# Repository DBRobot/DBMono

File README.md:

# DBMono

## Setup

After cloning, run the setup script from the repo root:

```bash
cd DBMono
./setup.sh
```

This will:
- Link KiCad templates to your local KiCad installation
- Set the `DBMONO_LIBS` environment variable in every installed KiCad version's
  config so that project library tables and 3D model paths using `${DBMONO_LIBS}`
  resolve to `<repo>/PCB_Hardware/libs`
- Link the VS Code C block-comment extension

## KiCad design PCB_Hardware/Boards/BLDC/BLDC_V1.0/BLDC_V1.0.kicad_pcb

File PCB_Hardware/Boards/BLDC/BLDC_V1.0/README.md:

# DBMono BLDC V1.0

This BLDC driver is designed as a general purpose brushless motor controller for robotics. Its focus is industrial grade performance at as low a cost as possible. Design requirements for this controller:
### Power
- Working voltage from 12-72V main input with daisy-chainable connectors
- Min 12A continuous current without cooling @60C
- 100A peak phase current
- Able to safely send regen current back to the bus or to a brake resistor
- Hot swap controller for safe hot plug and inrush control
- 5V logic input
- USBC logic input power delivery
- Short circuit protection
- Bidirectional reverse polarity protection
- Can survive +/- 100V transients

### Communication
- Daisy chain CANFD as the main communication interface
- USBC for configuration and live monitoring
- Dual SPI for up to 2 external encoders
- IO to support I2C, UART, ADC, TIM, and GPIO peripherals

### Sensing
- Onboard 21bit absolute magnetic encoder
- Onboard temperature sensor
- Optional off-board temperature sensor
- 4 Pin fan connector for PWM control and tachometer feedback

### Control Modes
- Sensorless FOC
- Position, velocity, and torque control
- Trajectory control
- Impedance control
- Anti-cogging compensation 
- Friction compensation
- Time synchronized commands
- Auto-tune

### Driver Parameters
- Switching  frequency of 45kHz

### Other
- ORing inputs for safe handling of multiple inputs
- EEPROM for configuration settings

## Gate Driver Design
The TI DRV8353SRTAR was selected for its low cost to performance and flexibility, as well as the high operating voltage. 
### FET Selection

#### Calculating Max $Q_g$ 
From 9.2.1.2.1 of the datasheet, the driver only supports fets that fall into the range given by the following equations:

![[Pasted image 20260510133448.png]] 

The design spec is up to 45kHz switching speed, and $I_{\text{VCP/VGLS}}$ is 25mA for all VM > 15V. While this design is technically specked to operate down to 12V, the target for performance is 24 and 48V motors. VM is fed by the input, so for the sake of this calculation the <15V scenario is ignored. 

**Trapezoidal Commutation**
$$
\begin{align}
&Q_g < \frac{I_{\text{VCP/VGLS}}}{f_{\text{PWM}}} \\
\\
&I_{\text{VCP/VGLS}} = 25mA \\
&f_{\text{PWM}} = 45kHz \\
\\
&Q_g < \frac{25 \times 10^{-3}\;A}{45 \times 10^3\;Hz}\\
&Q_g < 555\;nC
\end{align}
$$
**Sinusoidal Commutation**

$$
\begin{align}
&Q_g < \frac{I_{\text{VCP/VGLS}}}{3 \times f_{\text{PWM}}} \\
\\
&I_{\text{VCP/VGLS}} = 25mA \\
&f_{\text{PWM}} = 45kHz \\
\\
&Q_g < \frac{25 \times 10^{-3}\;A}{3 \times 45 \times 10^3\;Hz}\\
&Q_g < 185\;nC
\end{align}
$$

#### Calculating Max $R_{DS(ON)}$ 
From 9.2.1.2.3 in the datasheet, the overcurrent configuration is set via the equation bellow:

$$V_{DS\_OCP} > I_{max} \times R_{DS(ON)max}$$
As shown on the table in page 16 of the datasheet, the max setting for $V_{DS\_OCP}$ = 2V. Therefor:

$$
\begin{gathered}
R_{DS(ON)max} < \frac{V_{DS\_OCP}}{I_{max}} \\
\\
R_{DS(ON)max} < \frac{2V}{100A} \\
\\
R_{DS(ON)max} < 20m \Omega
\end{gathered}
$$

#### Selected FET - TPH3R70APL
This part was selected primarily for its thermal performance. In order to survive with 12A continuous current without a heat sink or other cooling solution, thermal performance is the most important aspect of fet selection. 

##### Min Rise Time
From the datasheet of the fet:

$$
Q_{gd}=14nC
$$

Then from the datasheet of the  DRV8353:
$$
\begin{array}{c c}
I_{DRIVEP} = \frac{Q_{gd}}{t_r} && I_{DRIVEN} = \frac{Q_{gd}}{t_f} \\
t_r > \frac{Q_{gd}}{I_{DRIVEP}} && t_f > \frac{Q_{gd}}{I_{DRIVEN}} \\
t_r > \frac{14nC}{1A} && t_f > \frac{14nC}{2A}\\
t_r > 14ns && t_f > 7ns
\end{array}
$$
##### Thermal Performance 
These calculations are done with no consideration for fans or other thermal management. This is done to establish the 12A no cooling baseline.

**Relevant Specs:**
$Q_g = 67nC < 185nC$
$T_{j\_max} = 175\degree C$ 
$R_{DS(ON)} \; @ \; T_{j\_max}= 9.25m\Omega$ 
$I_{peak} = I_D= 12 \times \sqrt 2 = 16.97A$
$t_r = 14ns$
$t_f = 19ns$

**Conduction Loss**
$$
\begin{gathered}
P_{cond} = I_{RMS}^2 \times R_{DS(ON)} \\
P_{cond} = (12A)^2 \times 0.00925 \Omega \\
P_{cond} = 1.33W
\end{gathered}
$$
**Switching Loss**
$$
\begin{gathered}
P_{sw} = \frac{1}{2} \times V_{BUS} \times I_D \times (t_r + t_f) \times f_{PWM} \\
P_{sw} = \frac{1}{2} \times 48V \times 16.97A \times  (14 \times 10^{-9} + 19 \times 10^{-9})s \times (45 \times 10^3) Hz \\
P_{sw} = 0.60W
\end{gathered}
$$

**Gate Charge Loss**
$$
\begin{gathered}
P_{gate} = Q_g \times V_{GS} \times f_{PWM} \\
P_{gate} = (67 \times 10^{-9})C \times 10V \times (45 \times 10^3)Hz \\
P_{gate} = 0.03W
\end{gathered}
$$

**Reverse Recovery Loss**

$$
\begin{gathered}
P_{rr} = Q_{rr} \times V_{BUS} \times f_{PWM} \\
P_{rr} = (74 \times 10^{-9})C \times 48V \times (45 \times 10^3)Hz \\
P_{rr} = 0.16W
\end{gathered}
$$
**Total Losses**
$$

P_{total} = 1.33 + 0.60 + 0.03 + 0.16 = 2.12W \\
$$
##### Copper Area Check
Using the total power loss of the FET, we can approximate the copper area needed to prevent the FET from failing. 

$$
\begin{gathered}
R_{\theta JA} < \frac{T_J - T_{ambient}}{P_{total}} \\
R_{\theta JA} < \frac{(175 - 60) \degree C}{2.12W} \\
R_{\theta JA} < 54.2 \degree C/W
\end{gathered}
$$

Application note Z8F80193346 from Infineon is used, as it is on a similar package, to sanity check the thermal limits given that there will be relatively little copper under each fet:
![[Pasted image 20260510212608.png]]

![[Pasted image 20260510212842.png]]
This implies that the board will need 12 thermal vias under the pad of the fet, with copper pour on both the top and bottom of them board. Single sided copper pour would be ill advised, but 2 layers of copper pour on the outer side of the board should be enough to keep thermals in check.

### Sense Amplifier Configuration
The DRV8353 uses shunt resistors to measure the current of each phase. To determine the resistance and gain values to use, the centered usable output voltage swing that the MCU can measure. Because a STM32G4 is used, $V_{VREF}=3.3V$.
$$
\begin{gathered}
V_O = (V_{VREF} - 0.25V) -\frac{V_{VREF}}{2} \\ \\
V_O = (3.3V-0.25V) - \frac{3.3V}{2} \\
V_O = 1.4V
\end{gathered}
$$

After calculating $V_O$, the resistance value $R$ can be calculated, where $A_V$ is the amplifier gain:

$$
\begin{aligned}
R &= \frac{V_O}{A_V \times I} & P_{SENSE} &> I_{RMS}^2 \times R 
\end{aligned}
$$

| | $A_V=5$ | $A_V=10$ | $A_V=20$ | $A_V=40$ |
|---|---|---|---|---|
| $R$ | $2.8m\Omega$ | $1.4m\Omega$ | $0.7m\Omega$ | $0.35m\Omega$ |
| $P_{SENSE}$ | $0.40W$ | $0.20W$ | $0.10W$ | $0.05W$ |
| $V_{DIFF}$ | $0.28V$ | $0.14V$ | $0.07V$ | $0.04V$ |

**Selected:** $A_V = 10$ with $R = 1m\Omega$. At $I_{max} = 100A$, $V_O = 1m\Omega \times 10 \times 100A = 1.0V$, keeping the amplifier output in the linear range with $0.4V$ of headroom in each direction. $1m\Omega$ is a standard value and $P_{SENSE} = 0.14W$ is easily handled by a 2512 package.

### DRV8353 Power Dissipation
Equations 26 and 27 from page 70 of the datasheet can be used to ensure that the gate driver itself does not overheat:

$$
\begin{aligned}
P_{VCP} &= I_{VCP} \times (V_{VM}+V_{VDRAIN}) & P_{VGLS} &= I_{VGLS} \times V_{VM} & P_{VM} &= I_{VM} \times V_{VM} \\
P_{VCP} &= 9mA \times (72V + 72V) & P_{VGLS} &= 9mA \times 72V & P_{VM} &= 15mA \times 72V \\
P_{VCP} &= 1.3W & P_{VGLS} &= 0.65W & P_{VM} &= 1.08W 
\end{aligned}
$$
$$
\begin{gathered}
P_{TOTAL} = 1.3W + 0.65W + 1.08W = 3.03W \\ 
R_{\theta JA} = 26.1 \\ \\
T_J = T_A + R_{\theta JA} \times P_{TOTAL} \\
T_J = 60 \degree C + (26.1 \times 3.03W) \\
T_J = 139 \degree C <150 \degree C
\end{gathered}
$$
### Input Bulk Capacitor

The DC link capacitor has two distinct jobs:

1. **Switching frequency bypass** (45kHz) — low-ESR MLCCs handle this trivially. Each 1206 MLCC handles $\sim 2A_{RMS}$ ripple. Only 3-4 are needed.
2. **Low-frequency energy storage** ($2\times$ electrical frequency, $\sim 100-1000$ Hz) — this drives the total capacitance. For a 12A motor at low speed, the DC link ripple current at $2\times f_e$ can be $4-6A_{RMS}$.

The DC bus current at 12A RMS phase current:

$$
I_{BUS} \approx \frac{3 \times V_{PHASE} \times I_{PHASE} \times \cos\phi}{V_{BUS} \times \eta}
\approx \frac{3 \times 26V \times 12A \times 0.9}{48V \times 0.9} \approx 20A
$$

Worst case switching-frequency ripple at $D=0.5$:

$$
C = \frac{I_{BUS} \times 0.25}{f_{PWM} \times \Delta V}
$$

| Condition | $I_{BUS}$ | $\Delta V=0.5V$ | $\Delta V=1V$ | $\Delta V=2V$ |
|---|---|---|---|---|
| 48V, 12A cont | 20A | $222\mu F$ | $111\mu F$ | $56\mu F$ |
| 72V, 12A cont | 14A | $156\mu F$ | $78\mu F$ | $39\mu F$ |
| 48V, 100A peak | 90A | $1000\mu F$ | $500\mu F$ | $250\mu F$ |

**Selected:**

| Part | Count | Value | Package | Purpose |
|------|-------|-------|---------|---------|
| C23 | 1 | $330\mu F$, 100V | Radial through-hole ($10\times 20$mm) | Bulk, handles $2\times f_e$ ripple |
| C25–C28 | 4 | $2.2\mu F$, 100V X7S | 1206 | Switching frequency bypass |
| CVM1 | 1 | $0.1\mu F$, 100V X7R | 0805 | Datasheet requirement at VM pin |

At 48V/12A: $\Delta V \approx 0.14V$ switching ripple, $\sim 3V$ peak at $2\times$ electrical frequency — well within DRV8353 headroom. At 100A peak transient: $\Delta V \approx 0.7V$. A single radial electrolytic is smaller than two 100V SMD equivalents, simpler to route, and handles the ripple current adequately since the battery sinks most of the low-frequency content and the MLCCs handle the 45kHz content.

### Hot-Swap Precharge (LM5069MM-2)

The LM5069MM-2 (U5) controls inrush via Rsns (R6 = 0.5mΩ, 2512) and Ctimer (C11 = 33nF, 0402). The pass FET is Q2 = IPT015N10N5 (100V/300A).

**Current limit** (Datasheet §6.5, V_sns_th = 50mV typical):

$$
I_{LIM} = \frac{V_{SNS\_TH}}{R_{SNS}} = \frac{50\text{mV}}{0.5\text{m}\Omega} = 100\text{A}
$$

**Inrush charge time** with C_load ≈ 340µF:

$$
t_{CHARGE} = \frac{C_{LOAD} \times V_{IN}}{I_{LIM}}
$$

| $V_{IN}$ | $t_{CHARGE}$ |
|----------|-------------|
| 48V | $340\mu F \times 48V / 100A = 163\mu s$ |
| 72V | $340\mu F \times 72V / 100A = 245\mu s$ |

**Fault timer** (Datasheet §7.3.2, I_timer = 85µA typical, V_timer_th = 1.25V):

$$
t_{FAULT} = \frac{C_{TIMER} \times V_{TIMER\_TH}}{I_{TIMER}} = \frac{33\text{nF} \times 1.25\text{V}}{85\mu\text{A}} = 485\mu\text{s}
$$

**Margin check** — t_fault > t_charge with >2× margin across all conditions:

| Condition | t_charge | t_fault | Margin |
|-----------|----------|---------|--------|
| 48V | 163µs | 485µs | 3.0× |
| 72V | 245µs | 485µs | 2.0× |
| 72V, I_timer max (110µA) | 245µs | 375µs | 1.5× |

## Change Notes

 - C14/C24 - footprint size needs to get larger. 10uF caps dont exist in that size
 -

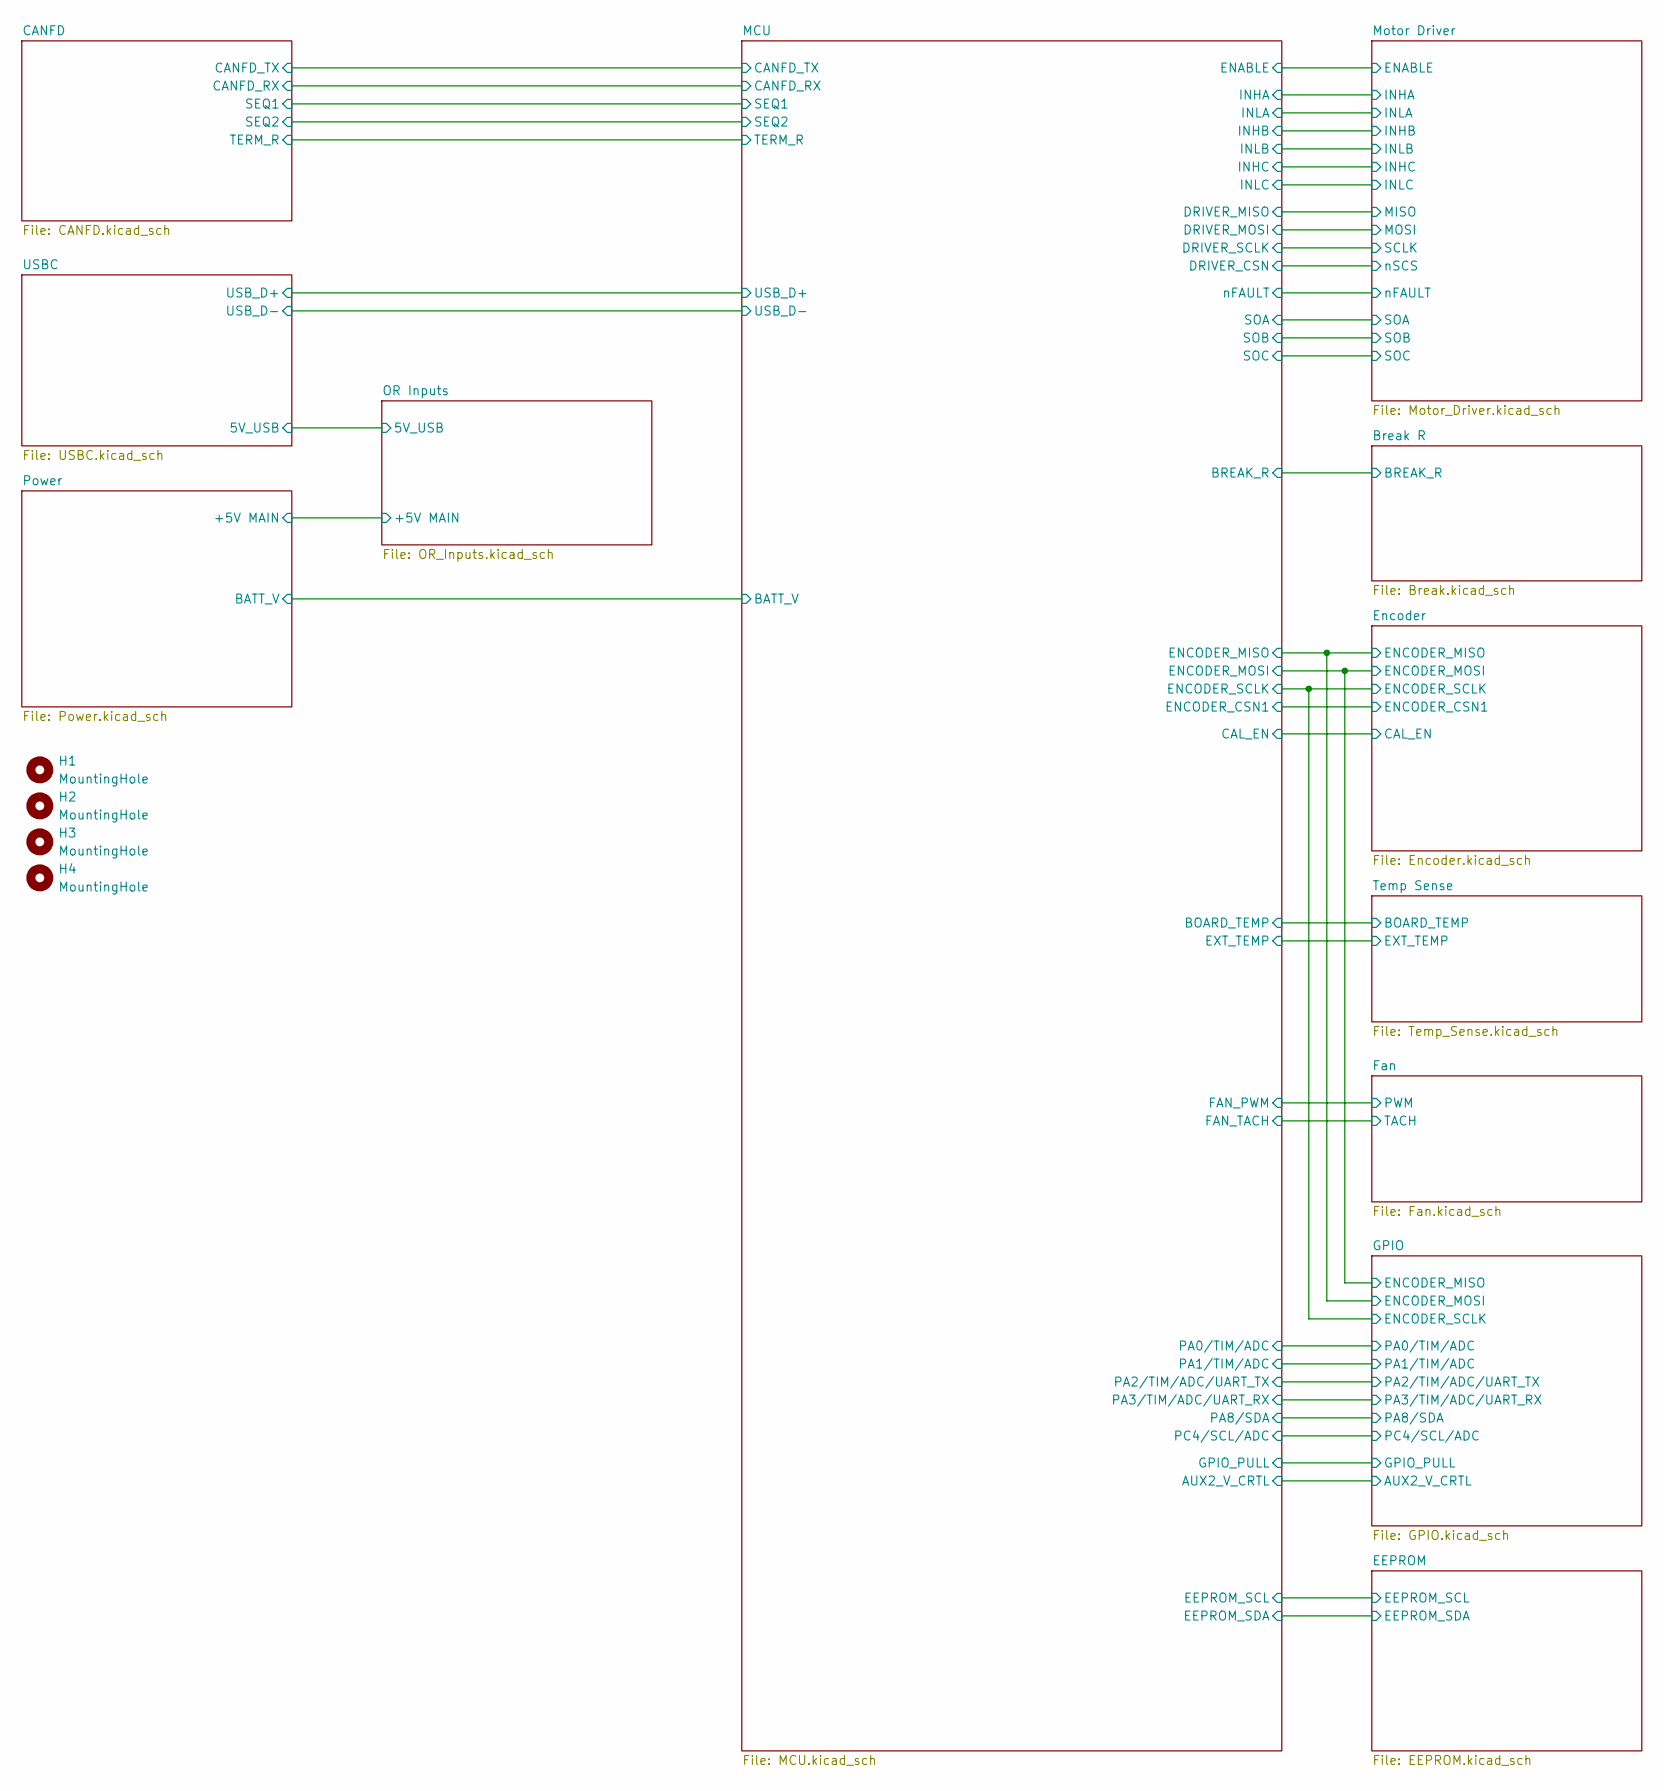
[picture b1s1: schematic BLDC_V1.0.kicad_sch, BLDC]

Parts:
H1, H2, H3, H4: MountingHole; MountingHole_3.2mm_M3

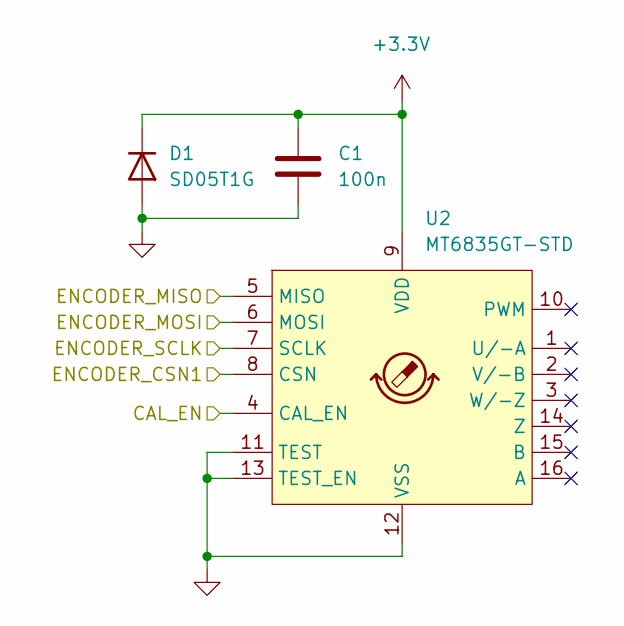
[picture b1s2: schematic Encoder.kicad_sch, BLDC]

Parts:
C1: 100n; C_0402_1005Metric; Manufacturer_Part_Number CC0402ZRY5V6BB104
D1: SD05T1G; D_SOD-323; Manufacturer_Part_Number SD05T1G
U2: MT6835GT-STD; TSSOP-16_4.4x5mm_P0.65mm; Manufacturer_Part_Number MT6835GT-STD

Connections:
+3.3V: C1.1, D1.1 (K), U2.9 (VDD); also elsewhere on the board
/Encoder/CAL_EN: U2.4 (CAL_EN); also elsewhere on the board
/Encoder/ENCODER_CSN1: U2.8 (CSN); also elsewhere on the board
/Encoder/ENCODER_MISO: U2.5 (MISO); also elsewhere on the board
/Encoder/ENCODER_MOSI: U2.6 (MOSI); also elsewhere on the board
/Encoder/ENCODER_SCLK: U2.7 (SCLK); also elsewhere on the board
GND: C1.2, D1.2 (A), U2.11 (TEST), U2.12 (VSS), U2.13 (TEST_EN); also elsewhere on the board

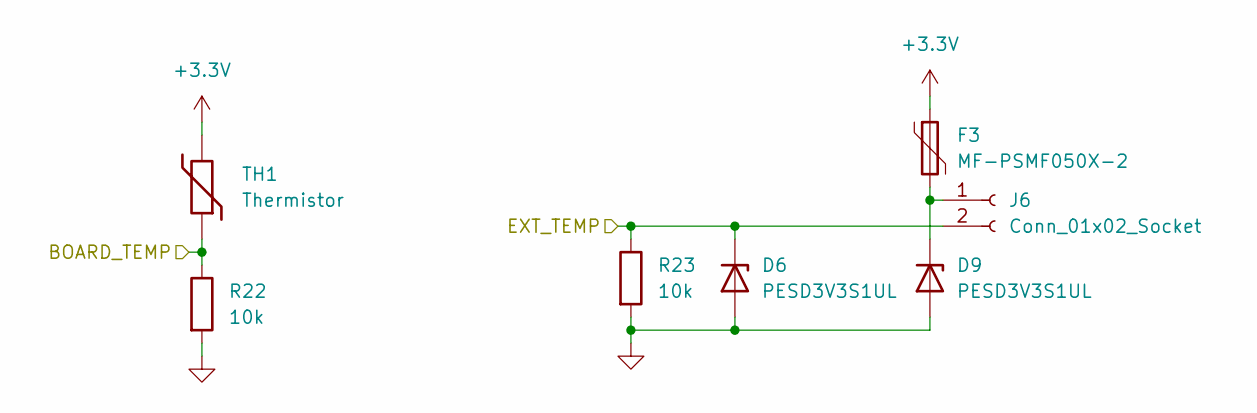
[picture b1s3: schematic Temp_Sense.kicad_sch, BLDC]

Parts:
D6, D9: PESD3V3S1UL; D_SOD-882
F3: MF-PSMF050X-2; Fuse_0805_2012Metric; Manufacturer_Part_Number MF-PSMF050X-2
J6: Conn_01x02_Socket; JST_GH_SM02B-GHS-TB_1x02-1MP_P1.25mm_Horizontal
R22, R23: 10k; R_0402_1005Metric; Manufacturer_Part_Number HP02WAJ0103TCE
TH1: Thermistor; R_0603_1608Metric

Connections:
+3.3V: F3.1, TH1.2; also elsewhere on the board
/MCU/BOARD_TEMP: R22.1, TH1.1; also elsewhere on the board
/MCU/EXT_TEMP: D6.1 (K), J6.2, R23.1; also elsewhere on the board
GND: D6.2 (A), D9.2 (A), R22.2, R23.2; also elsewhere on the board
unnamed: D9.1 (K), F3.2, J6.1

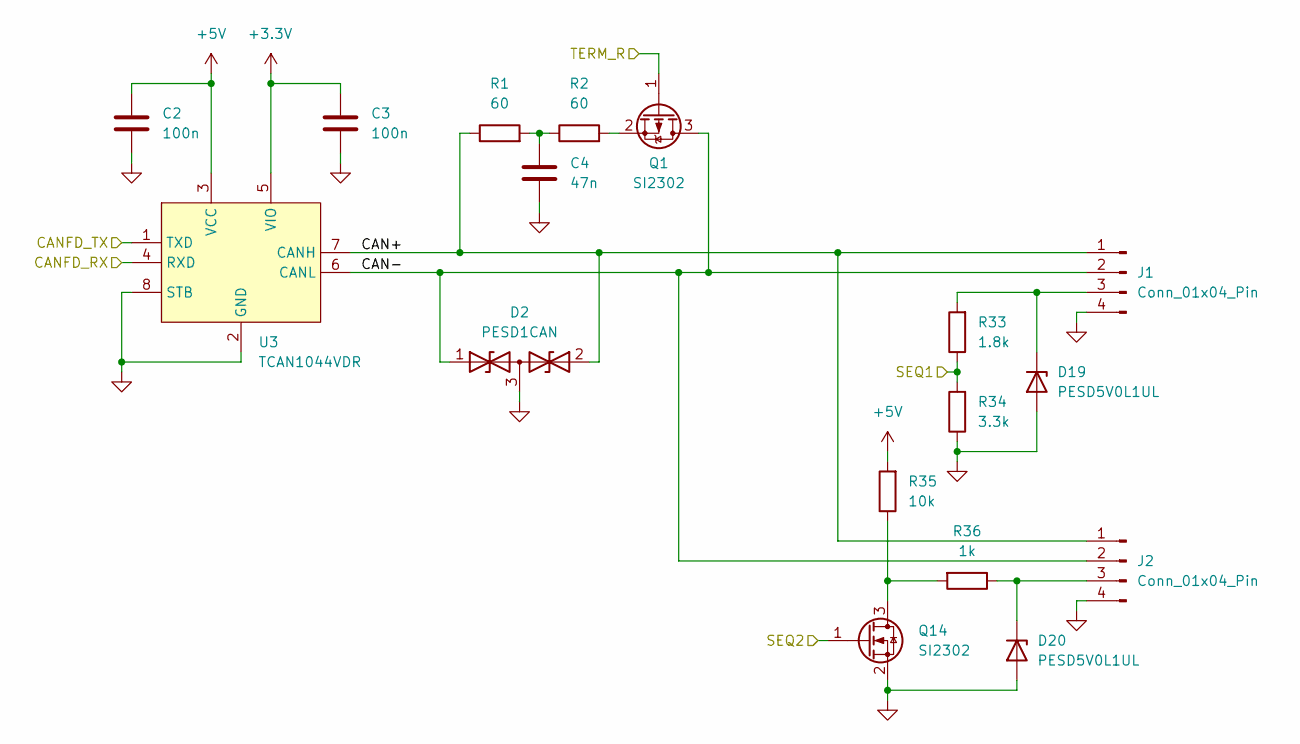
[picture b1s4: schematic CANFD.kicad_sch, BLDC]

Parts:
C2, C3: 100n; C_0402_1005Metric; Manufacturer_Part_Number CC0402ZRY5V6BB104
C4: 47n; C_0402_1005Metric; Manufacturer_Part_Number CC0402JRX7R6BB473
D2: PESD1CAN; SOT-23
D19, D20: PESD5V0L1UL; D_SOD-882
J1, J2: Conn_01x04_Pin; CONN_JST_SM04B-PASS; Manufacturer_Part_Number JST SM04B-PASS-TB(LF)(SN)
Q1, Q14: SI2302; SOT-23; Manufacturer_Part_Number Si2302CDS-T1-GE3
R1, R2: 60; R_0805_2012Metric; Manufacturer_Part_Number CQ05W8F604JT5E
R33: 1.8k; R_0402_1005Metric; Manufacturer_Part_Number 0402WGJ0182TCE
R34: 3.3k; R_0402_1005Metric; Manufacturer_Part_Number RC0402JR-073K3L
R35: 10k; R_0402_1005Metric; Manufacturer_Part_Number HP02WAJ0103TCE
R36: 1k; R_0402_1005Metric; Manufacturer_Part_Number CQ02WGJ0102TCE
U3: TCAN1044VDR; SOIC-8_3.9x4.9mm_P1.27mm; Manufacturer_Part_Number TCAN1044VDR

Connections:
+3.3V: C3.1, U3.5 (VIO); also elsewhere on the board
+5V: C2.1, R35.2, U3.3 (VCC); also elsewhere on the board
/CANFD/CAN+: D2.2 (A2), J1.1, J2.1, R1.1, U3.7 (CANH)
/CANFD/CAN-: D2.1 (A1), J1.2, J2.2, Q1.3 (D), U3.6 (CANL)
/CANFD/CANFD_RX: U3.4 (RXD); also elsewhere on the board
/CANFD/CANFD_TX: U3.1 (TXD); also elsewhere on the board
/CANFD/SEQ1: R33.1, R34.2; also elsewhere on the board
/CANFD/SEQ2: Q14.1 (G); also elsewhere on the board
/CANFD/TERM_R: Q1.1 (G); also elsewhere on the board
GND: C2.2, C3.2, C4.2, D2.3 (common), D19.2 (A), D20.2 (A), J1.4, J2.4, Q14.2 (S), R34.1, U3.2 (GND), U3.8 (STB); also elsewhere on the board
unnamed: C4.1, R1.2, R2.1
unnamed: D19.1 (K), J1.3, R33.2
unnamed: D20.1 (K), J2.3, R36.1
unnamed: Q1.2 (S), R2.2
unnamed: Q14.3 (D), R35.1, R36.2

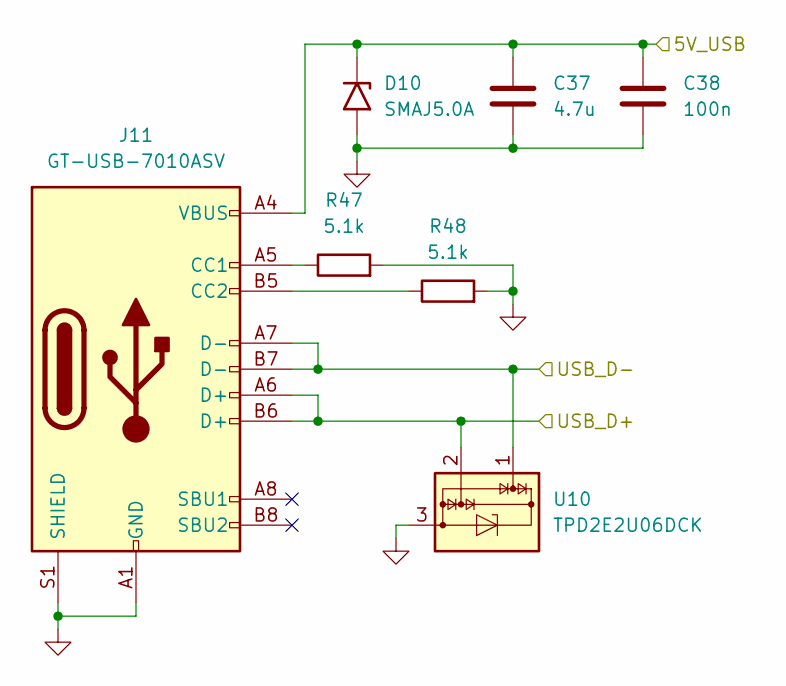
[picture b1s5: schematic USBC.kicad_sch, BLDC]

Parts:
C37: 4.7u; C_0603_1608Metric; Manufacturer_Part_Number CL10A475MQ8NNNC
C38: 100n; C_0402_1005Metric; Manufacturer_Part_Number CC0402ZRY5V6BB104
D10: SMAJ5.0A; D_SMA
J11: GT-USB-7010ASV; USB_C_Receptacle_G-Switch_GT-USB-7010ASV; Manufacturer_Part_Number GT-USB-7010ASV
R47, R48: 5.1k; R_0402_1005Metric; Manufacturer_Part_Number RC0402JR-075K1L
U10: TPD2E2U06DCK; SOT-323_SC-70; Manufacturer_Part_Number TPD2E2U06DCK

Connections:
/MCU/USB_D+: J11.A6 (D+), J11.B6 (D+), U10.2; also elsewhere on the board
/MCU/USB_D-: J11.A7 (D-), J11.B7 (D-), U10.1; also elsewhere on the board
/OR Inputs/5V_USB: C37.1, C38.1, D10.1 (A1), J11.A4 (VBUS), J11.A9 (VBUS), J11.B4 (VBUS), J11.B9 (VBUS); also elsewhere on the board
GND: C37.2, C38.2, D10.2 (A2), J11.A1 (GND), J11.A12 (GND), J11.B1 (GND), J11.B12 (GND), J11.S1 (SHIELD), R47.2, R48.2, U10.3; also elsewhere on the board
unnamed: J11.A5 (CC1), R47.1
unnamed: J11.B5 (CC2), R48.1

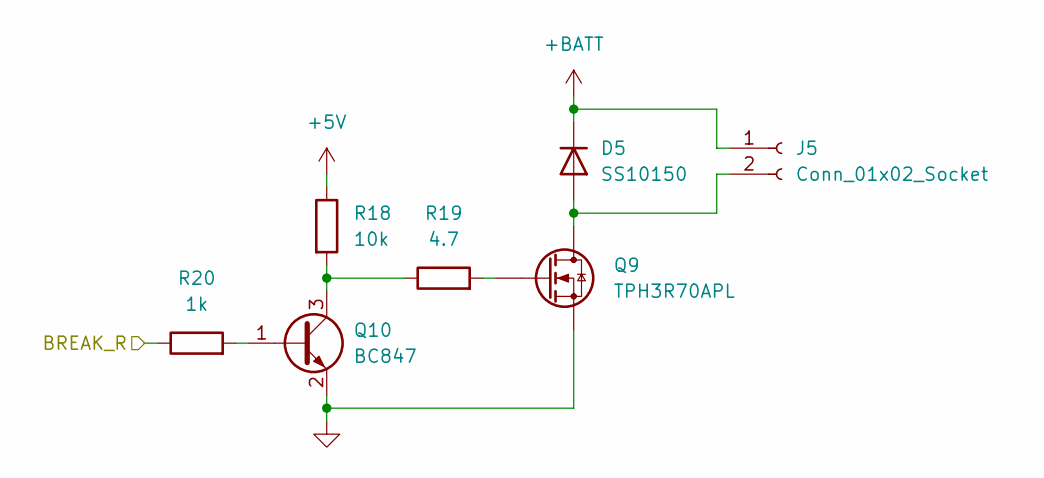
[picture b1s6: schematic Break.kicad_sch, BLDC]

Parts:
D5: SS10150; D_SOD-123F; Manufacturer_Part_Number SS10150
J5: Conn_01x02_Socket; JST_XH_S2B-XH-A-1_1x02_P2.50mm_Horizontal
Q9: TPH3R70APL; SOP AdvanceN_TOS; Manufacturer_Part_Number TPH3R70APL
Q10: BC847; SOT-23
R18: 10k; R_0402_1005Metric; Manufacturer_Part_Number HP02WAJ0103TCE
R19: 4.7; R_0402_1005Metric; Manufacturer_Part_Number 0402WGJ047JTCE
R20: 1k; R_0402_1005Metric; Manufacturer_Part_Number CQ02WGJ0102TCE

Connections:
+5V: R18.1; also elsewhere on the board
+BATT: D5.1 (K), J5.1; also elsewhere on the board
/Break R/BREAK_R: R20.1; also elsewhere on the board
GND: Q9.1 (S), Q9.2 (S), Q9.3 (S), Q10.2 (E); also elsewhere on the board
unnamed: D5.2 (A), J5.2, Q9.5 (D), Q9.6 (D), Q9.7 (D), Q9.8 (D)
unnamed: Q9.4 (G), R19.2
unnamed: Q10.1 (B), R20.2
unnamed: Q10.3 (C), R18.2, R19.1

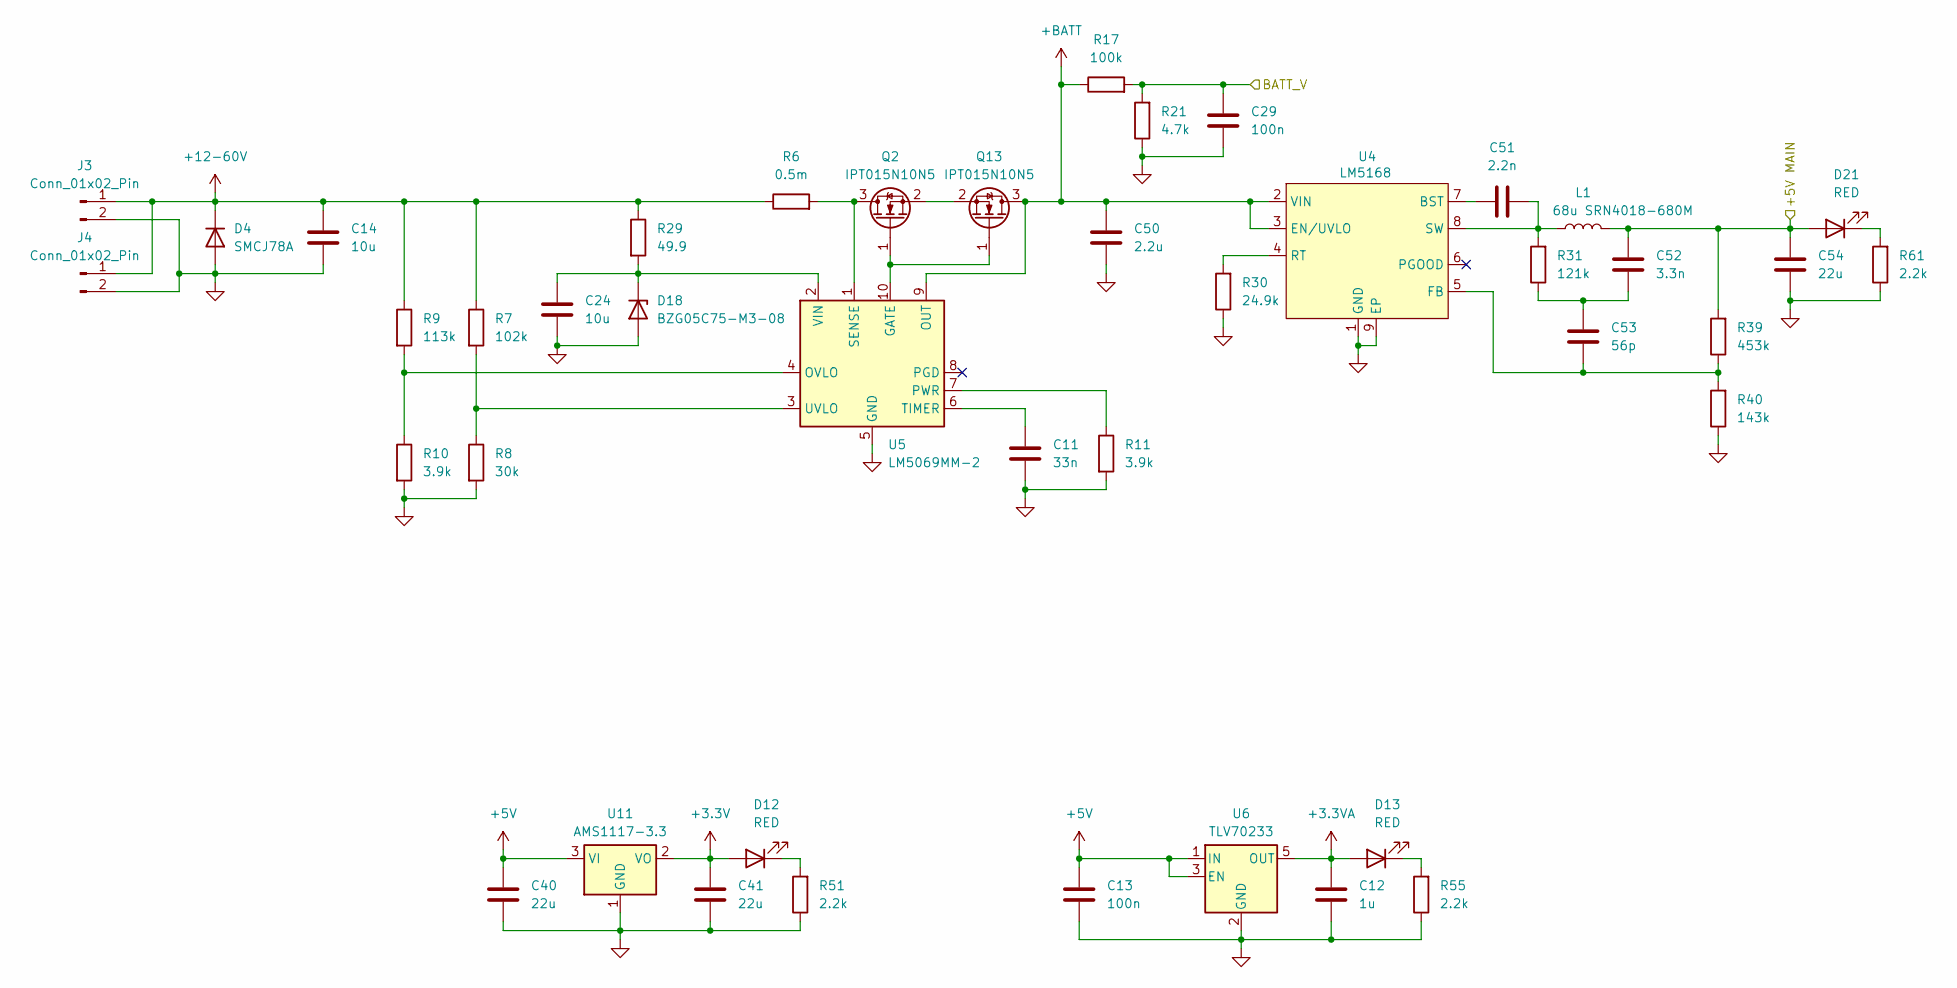
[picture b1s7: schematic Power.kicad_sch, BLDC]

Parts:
C11: 33n; C_0402_1005Metric; Manufacturer_Part_Number CC0402MRX7R7BB333
C12: 1u; C_0603_1608Metric; Manufacturer_Part_Number CC0603ZRY5V6BB105
C13: 100n; C_0402_1005Metric; Manufacturer_Part_Number CC0402ZRY5V6BB104
C14, C24: 10u; C_0603_1608Metric; Manufacturer_Part_Number JMK107BJ106KA-T
C29: 100n; C_0402_1005Metric; Manufacturer_Part_Number GRM155R62A104KE14D
C40, C41, C54: 22u; C_0805_2012Metric; Manufacturer_Part_Number CC0805KRX7R0BB681
C50: 2.2u; C_0805_2012Metric; Manufacturer_Part_Number GRM21BD72A225ME01L
C51: 2.2n; C_0402_1005Metric; Manufacturer_Part_Number CC0402MRX7R6BB222
C52: 3.3n; C_0402_1005Metric; Manufacturer_Part_Number CC0402KRX7R7BB332
C53: 56p; C_0402_1005Metric; Manufacturer_Part_Number CC0402GRNPO9BN560
D4: SMCJ78A; D_SMC
D12, D13, D21: RED; LED_0603_1608Metric; Manufacturer_Part_Number XINGLIGHT XL-1608SURC-06
D18: BZG05C75-M3-08; D_SMA; Manufacturer_Part_Number BZG05C75-M3-08
J3, J4: Conn_01x02_Pin; AMASS_XT30PW-M_1x02_P2.50mm_Horizontal; Manufacturer_Part_Number XT30PW-M30.G.Y
L1: 68u SRN4018-680M; L_Bourns-SRN4018; Manufacturer_Part_Number SRN4018-680M
Q2, Q13: IPT015N10N5; Infineon_PG-HSOF-8-1; Manufacturer_Part_Number IPT015N10N5
R6: 0.5m; R_2512_6332Metric; Manufacturer_Part_Number WSL2512L5000FEA18
R7: 102k; R_0805_2012Metric; Manufacturer_Part_Number 0805W8F1023T5E
R8: 30k; R_0805_2012Metric; Manufacturer_Part_Number 0805W8J0303T5E
R9: 113k; R_0805_2012Metric; Manufacturer_Part_Number 0805W8F1133T5E
R10: 3.9k; R_0805_2012Metric; Manufacturer_Part_Number 0805W8J0392T5E
R11: 3.9k; R_0402_1005Metric; Manufacturer_Part_Number CQ02WGF3901TCE
R17: 100k; R_0603_1608Metric; Manufacturer_Part_Number CQ03WAJ0104T5E
R21: 4.7k; R_0603_1608Metric; Manufacturer_Part_Number 0603WAF3032T5S
R29: 49.9; R_0805_2012Metric; Manufacturer_Part_Number 0805W8F499JT5E
R30: 24.9k; R_0402_1005Metric; Manufacturer_Part_Number RC0402FR-0724K9L
R31: 121k; R_0402_1005Metric; Manufacturer_Part_Number 0402WGF1213TCE
R39: 453k; R_0402_1005Metric; Manufacturer_Part_Number CRCW0402453KFKED
R40: 143k; R_0402_1005Metric; Manufacturer_Part_Number 0402WGF1433TCE
R51, R55, R61: 2.2k; R_0402_1005Metric; Manufacturer_Part_Number 0402WGJ0222TCE
U4: LM5168; SOIC-8-1EP_3.9x4.9mm_P1.27mm_EP2.29x3mm; Manufacturer_Part_Number LM5168
U5: LM5069MM-2; MSOP-10_3x3mm_P0.5mm; Manufacturer_Part_Number LM5069MM-2
U6: TLV70233; SOT-23-5; Manufacturer_Part_Number TLV70233
U11: AMS1117-3.3; SOT-223-3_TabPin2; Manufacturer_Part_Number AMS1117-3.3

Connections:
+3.3V: C41.1, D12.2 (A), U11.2 (VO); also elsewhere on the board
+3.3VA: C12.1, D13.2 (A), U6.5 (OUT); also elsewhere on the board
+5V: C13.1, C40.1, U6.1 (IN), U6.3 (EN), U11.3 (VI); also elsewhere on the board
+12-60V: C14.1, D4.1 (K), J3.1, J4.1, R6.1, R7.1, R9.1, R29.1
+BATT: C50.1, Q13.3 (D), R17.1, U4.2 (VIN), U4.3 (EN/UVLO), U5.9 (OUT); also elsewhere on the board
/MCU/BATT_V: C29.1, R17.2, R21.2; also elsewhere on the board
/OR Inputs/+5V MAIN: C52.2, C54.1, D21.2 (A), L1.2, R39.2; also elsewhere on the board
GND: C11.2, C12.2, C13.2, C14.2, C24.2, C29.2, C40.2, C41.2, C50.2, C54.2, D4.2 (A), D18.2 (A), J3.2, J4.2, R8.2, R10.2, R11.2, R21.1, R30.1, R40.1, R51.1, R55.1, R61.1, U4.1 (GND), U4.9 (EP), U5.5 (GND), U6.2 (GND), U11.1 (GND); also elsewhere on the board
unnamed: C52.1, C53.2, R31.1
unnamed: D12.1 (K), R51.2
unnamed: D13.1 (K), R55.2
unnamed: C24.1, D18.1 (K), R29.2, U5.2 (VIN)
unnamed: D21.1 (K), R61.2
unnamed: Q2.3 (D), R6.2, U5.1 (SENSE)
unnamed: Q2.1 (G), Q13.1 (G), U5.10 (GATE)
unnamed: Q2.2 (S), Q13.2 (S)
unnamed: C51.1, U4.7 (BST)
unnamed: C53.1, R39.1, R40.2, U4.5 (FB)
unnamed: R30.2, U4.4 (RT)
unnamed: C51.2, L1.1, R31.2, U4.8 (SW)
unnamed: R9.2, R10.1, U5.4 (OVLO)
unnamed: R11.1, U5.7 (PWR)
unnamed: C11.1, U5.6 (TIMER)
unnamed: R7.2, R8.1, U5.3 (UVLO)

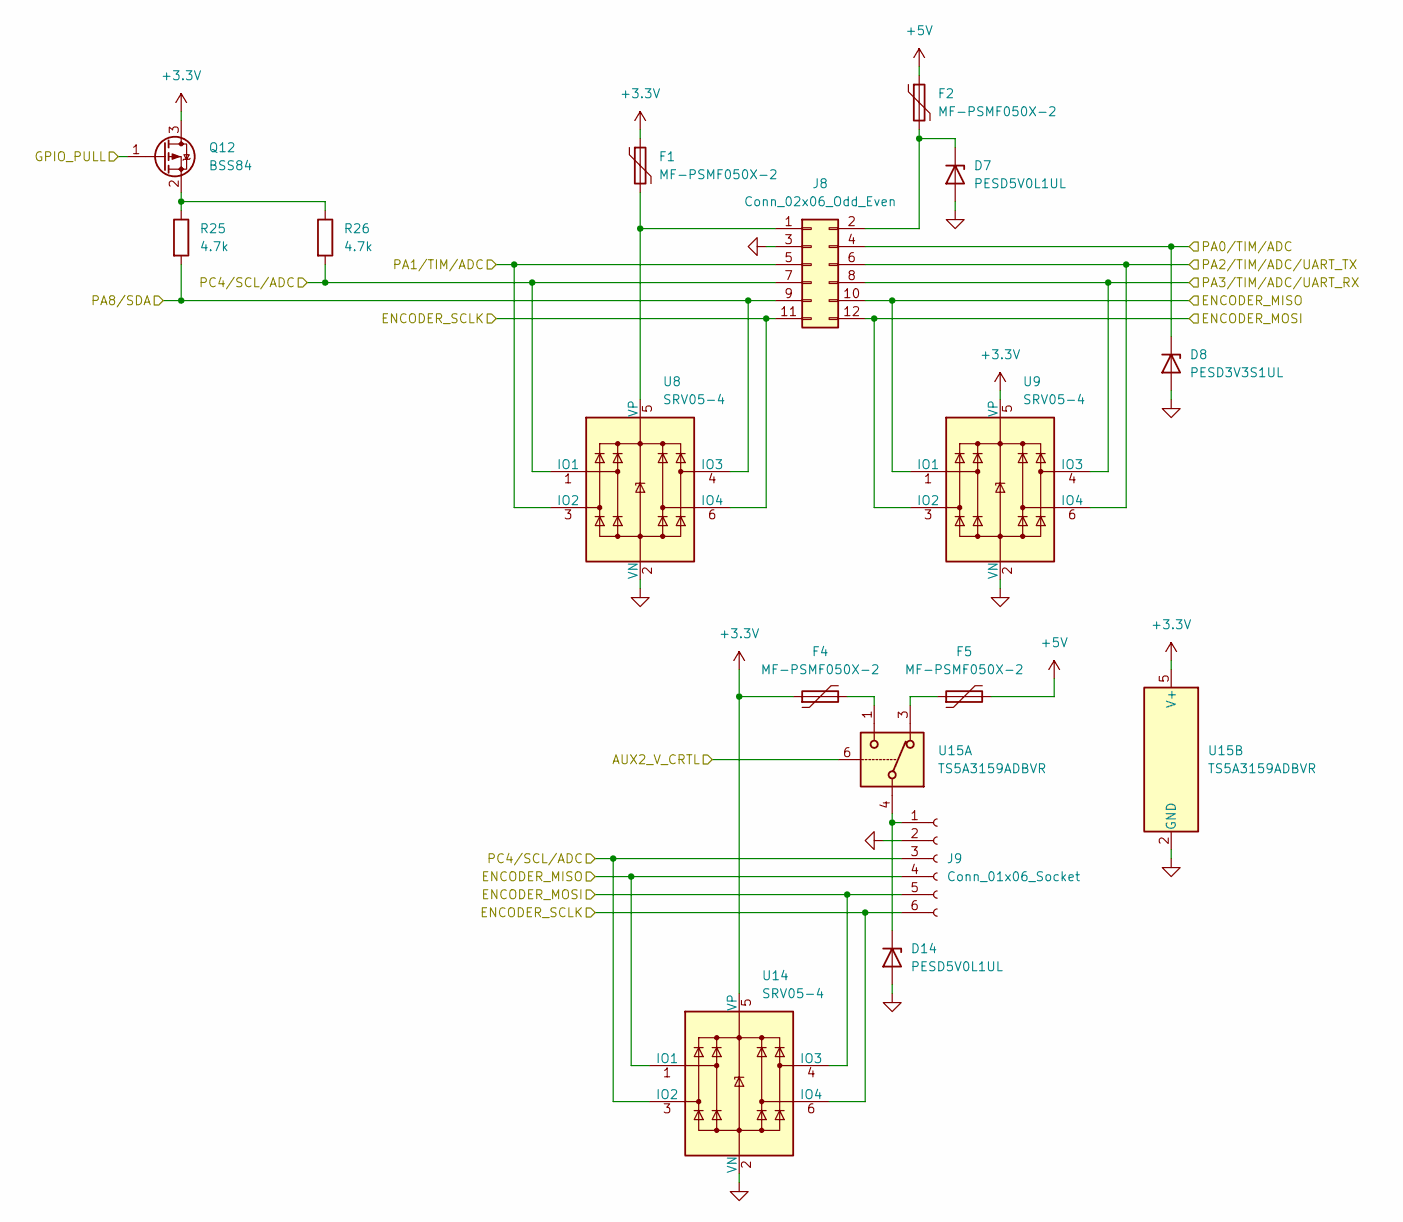
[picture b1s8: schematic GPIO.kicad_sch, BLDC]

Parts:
D7, D14: PESD5V0L1UL; D_SOD-882
D8: PESD3V3S1UL; D_SOD-882
F1, F2, F4, F5: MF-PSMF050X-2; Fuse_0805_2012Metric; Manufacturer_Part_Number MF-PSMF050X-2
J8: Conn_02x06_Odd_Even; JST_PUD_B12B-PUDSS_2x06_P2.00mm_Vertical
J9: Conn_01x06_Socket; JST_GH_SM06B-GHS-TB_1x06-1MP_P1.25mm_Horizontal
Q12: BSS84; SOT-23
R25, R26: 4.7k; R_0402_1005Metric; Manufacturer_Part_Number CQ02WGF4701TCE
U8, U9, U14: SRV05-4; SOT-23-6; Manufacturer_Part_Number SRV05-4
U15: TS5A3159ADBVR; SOT-23-6; Manufacturer_Part_Number TS5A3159ADBVR

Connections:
+3.3V: F1.1, F4.1, Q12.3 (D), U9.5 (VP), U14.5 (VP), U15.5 (V+); also elsewhere on the board
+5V: F2.1, F5.2; also elsewhere on the board
/Encoder/ENCODER_MISO: J8.12, J9.5, U9.3 (IO2), U14.4 (IO3); also elsewhere on the board
/Encoder/ENCODER_MOSI: J8.10, J9.4, U9.1 (IO1), U14.1 (IO1); also elsewhere on the board
/Encoder/ENCODER_SCLK: J8.11, J9.6, U8.6 (IO4), U14.6 (IO4); also elsewhere on the board
/GPIO/AUX2_V_CRTL: U15.6; also elsewhere on the board
/GPIO/GPIO_PULL: Q12.1 (G); also elsewhere on the board
/GPIO/PA0/TIM/ADC: D8.1 (K), J8.4; also elsewhere on the board
/GPIO/PA1/TIM/ADC: J8.5, U8.3 (IO2); also elsewhere on the board
/GPIO/PA2/TIM/ADC/UART_TX: J8.6, U9.6 (IO4); also elsewhere on the board
/GPIO/PA3/TIM/ADC/UART_RX: J8.8, U9.4 (IO3); also elsewhere on the board
/GPIO/PA8/SDA: J8.9, R25.2, U8.4 (IO3); also elsewhere on the board
/GPIO/PC4/SCL/ADC: J8.7, J9.3, R26.2, U8.1 (IO1), U14.3 (IO2); also elsewhere on the board
GND: D7.2 (A), D8.2 (A), D14.2 (A), J8.3, J9.2, U8.2 (VN), U9.2 (VN), U14.2 (VN), U15.2 (GND); also elsewhere on the board
unnamed: D7.1 (K), F2.2, J8.2
unnamed: D14.1 (K), J9.1, U15.4
unnamed: F4.2, U15.1
unnamed: F5.1, U15.3
unnamed: F1.2, J8.1, U8.5 (VP)
unnamed: Q12.2 (S), R25.1, R26.1

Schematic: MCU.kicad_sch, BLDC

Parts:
C30: 4.7u; C_0603_1608Metric; Manufacturer_Part_Number CL10A475MQ8NNNC
C31, C32, C33, C34, C35, C36, C42, C45: 100n; C_0402_1005Metric; Manufacturer_Part_Number CC0402ZRY5V6BB104
C43, C44: 18p; C_0402_1005Metric; Manufacturer_Part_Number CC0402JRNPO8BN180; JLCPCB Part Number C52923
J7: Conn_ARM_SWD_TagConnect_TC2030; Tag-Connect_TC2030-IDC-FP_2x03_P1.27mm_Vertical; not fitted
R24: 0; R_0402_1005Metric; Manufacturer_Part_Number RC0402JR-130RL
U7: STM32G474RET6; LQFP-64_10x10mm_P0.5mm; Manufacturer_Part_Number STM32G474RET6
Y2: XXGBBCNANF-25.000000MHZ; Crystal_SMD_3225-4Pin_3.2x2.5mm; Manufacturer_Part_Number XXGBBCNANF-25.000000MHZ

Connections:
+3.3V: C30.1, C31.1, C32.1, C33.1, C34.1, C35.1, J7.1 (VCC), U7.1 (VBAT), U7.16 (VDD), U7.32 (VDD), U7.48 (VDD), U7.64 (VDD); also elsewhere on the board
+3.3VA: C36.1, C42.1, U7.28 (VREF+), U7.29 (VDDA); also elsewhere on the board
/Break R/BREAK_R: U7.26 (PB2); also elsewhere on the board
/CANFD/CANFD_RX: U7.58 (PB5); also elsewhere on the board
/CANFD/CANFD_TX: U7.59 (PB6); also elsewhere on the board
/CANFD/SEQ1: U7.23 (PC5); also elsewhere on the board
/CANFD/SEQ2: U7.2 (PC13); also elsewhere on the board
/CANFD/TERM_R: U7.55 (PD2); also elsewhere on the board
/EEPROM/EEPROM_SCL: U7.61 (PB8); also elsewhere on the board
/EEPROM/EEPROM_SDA: U7.60 (PB7); also elsewhere on the board
/Encoder/CAL_EN: U7.9 (PC1); also elsewhere on the board
/Encoder/ENCODER_CSN1: U7.51 (PA15); also elsewhere on the board
/Encoder/ENCODER_MISO: U7.53 (PC11); also elsewhere on the board
/Encoder/ENCODER_MOSI: U7.54 (PC12); also elsewhere on the board
/Encoder/ENCODER_SCLK: U7.52 (PC10); also elsewhere on the board
/Fan/PWM: U7.62 (PB9); also elsewhere on the board
/Fan/TACH: U7.57 (PB4); also elsewhere on the board
/GPIO/AUX2_V_CRTL: U7.3 (PC14); also elsewhere on the board
/GPIO/GPIO_PULL: U7.4 (PC15); also elsewhere on the board
/GPIO/PA0/TIM/ADC: U7.12 (PA0); also elsewhere on the board
/GPIO/PA1/TIM/ADC: U7.13 (PA1); also elsewhere on the board
/GPIO/PA2/TIM/ADC/UART_TX: U7.14 (PA2); also elsewhere on the board
/GPIO/PA3/TIM/ADC/UART_RX: U7.17 (PA3); also elsewhere on the board
/GPIO/PA8/SDA: U7.42 (PA8); also elsewhere on the board
/GPIO/PC4/SCL/ADC: U7.22 (PC4); also elsewhere on the board
/MCU/BATT_V: U7.8 (PC0); also elsewhere on the board
/MCU/BOARD_TEMP: U7.10 (PC2); also elsewhere on the board
/MCU/DRIVER_CSN: U7.21 (PA7); also elsewhere on the board
/MCU/DRIVER_MISO: U7.20 (PA6); also elsewhere on the board
/MCU/DRIVER_MOSI: U7.18 (PA4); also elsewhere on the board
/MCU/DRIVER_SCLK: U7.19 (PA5); also elsewhere on the board
/MCU/ENABLE: U7.44 (PA10); also elsewhere on the board
/MCU/EXT_TEMP: U7.11 (PC3); also elsewhere on the board
/MCU/HSE IN: R24.2, U7.5 (PF0)
/MCU/HSE OUT: C44.1, U7.6 (PF1), Y2.3
/MCU/INHA: U7.37 (PB15); also elsewhere on the board
/MCU/INHB: U7.40 (PC8); also elsewhere on the board
/MCU/INHC: U7.38 (PC6); also elsewhere on the board
/MCU/INLA: U7.36 (PB14); also elsewhere on the board
/MCU/INLB: U7.41 (PC9); also elsewhere on the board
/MCU/INLC: U7.39 (PC7); also elsewhere on the board
/MCU/NRST: C45.2, U7.7 (PG10)
/MCU/SOA: U7.24 (PB0), U7.43 (PA9); also elsewhere on the board
/MCU/SOB: U7.25 (PB1), U7.35 (PB13); also elsewhere on the board
/MCU/SOC: U7.33 (PB11), U7.34 (PB12); also elsewhere on the board
/MCU/SWCLK: J7.4 (SWCLK), U7.50 (PA14)
/MCU/SWDIO: J7.2 (SWDIO), U7.49 (PA13)
/MCU/SWO: J7.6 (SWO), U7.56 (PB3)
/MCU/USB_D+: U7.46 (PA12); also elsewhere on the board
/MCU/USB_D-: U7.45 (PA11); also elsewhere on the board
/MCU/nFAULT: U7.30 (PB10); also elsewhere on the board
GND: C30.2, C31.2, C32.2, C33.2, C34.2, C35.2, C36.2, C42.2, C43.2, C44.2, C45.1, J7.5 (GND), U7.15 (VSS), U7.27 (VSSA), U7.31 (VSS), U7.47 (VSS), U7.63 (VSS), Y2.2, Y2.4; also elsewhere on the board
unnamed: C43.1, R24.1, Y2.1

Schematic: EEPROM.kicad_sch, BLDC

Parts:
C46: 100n; C_0402_1005Metric; Manufacturer_Part_Number CC0402ZRY5V6BB104
R27, R28: 4.7k; R_0402_1005Metric; Manufacturer_Part_Number CQ02WGF4701TCE
U16: CAT24C512C8UTR; Manufacturer_Part_Number CAT24C512C8UTR

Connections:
+3.3V: C46.1, R27.1, R28.1, U16.8 (VCC); also elsewhere on the board
/EEPROM/EEPROM_SCL: R28.2, U16.6 (SCL); also elsewhere on the board
/EEPROM/EEPROM_SDA: R27.2, U16.5 (SDA); also elsewhere on the board
GND: C46.2, U16.1 (A0), U16.2 (A1), U16.3 (A2), U16.4 (GND), U16.7 (WP); also elsewhere on the board

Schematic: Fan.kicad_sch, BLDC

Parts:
C57: 100n; C_0402_1005Metric; Manufacturer_Part_Number CC0402ZRY5V6BB104
D22, D24: PESD5V0S1UL; D_SOD-882
D23: PESD3V3S1UL; D_SOD-882
F6: MF-PSMF050X-2; Fuse_1812_4532Metric; Manufacturer_Part_Number MF-PSMF050X-2
J14: 47053-1000; FanPinHeader_1x04_P2.54mm_Vertical
Q11: BSS138; SOT-23
R56: 100; R_0402_1005Metric; Manufacturer_Part_Number RC0402JR-13100RL
R57: 100k; R_0402_1005Metric; Manufacturer_Part_Number CQ02WGJ0104TCE
R58, R59: 10k; R_0402_1005Metric; Manufacturer_Part_Number HP02WAJ0103TCE
R60: 1k; R_0402_1005Metric; Manufacturer_Part_Number CQ02WGJ0102TCE

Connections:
+3.3V: R59.2; also elsewhere on the board
+5V: F6.1, R58.2; also elsewhere on the board
/Fan/PWM: R56.1; also elsewhere on the board
/Fan/TACH: R59.1, R60.2; also elsewhere on the board
GND: C57.2, D22.2 (A), D23.2 (A), D24.2 (A), J14.1, Q11.2 (S), R57.1; also elsewhere on the board
unnamed: C57.1, D22.1 (K), J14.4, Q11.3 (D), R58.1
unnamed: D23.1 (K), J14.3, R60.1
unnamed: D24.1 (K), F6.2, J14.2
unnamed: Q11.1 (G), R56.2, R57.2

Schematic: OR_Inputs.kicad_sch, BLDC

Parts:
C39: 10u; C_0402_1005Metric; Manufacturer_Part_Number CL05A106MP5NUNC
D11: RED; LED_0603_1608Metric; Manufacturer_Part_Number XINGLIGHT XL-1608SURC-06
R49, R52, R53, R54: 100k; R_0402_1005Metric; Manufacturer_Part_Number CQ02WGJ0104TCE
R50: 5.1k; R_0402_1005Metric; Manufacturer_Part_Number RC0402JR-075K1L
U12, U13: LM66100DCK; SOT-363_SC-70-6; Manufacturer_Part_Number LM66100DCK

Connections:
+5V: C39.1, D11.2 (A), R49.1, U12.6 (VOUT), U13.6 (VOUT); also elsewhere on the board
/OR Inputs/5V_USB: R53.2, U13.1 (VIN); also elsewhere on the board
/OR Inputs/+5V MAIN: R52.1, U12.1 (VIN); also elsewhere on the board
GND: C39.2, R49.2, R50.1, U12.2 (GND), U13.2 (GND); also elsewhere on the board
unnamed: D11.1 (K), R50.2
unnamed: R52.2, R54.1, U12.5 (ST)
unnamed: R53.1, U12.3 (~CE)
unnamed: R54.2, U13.3 (~CE)
